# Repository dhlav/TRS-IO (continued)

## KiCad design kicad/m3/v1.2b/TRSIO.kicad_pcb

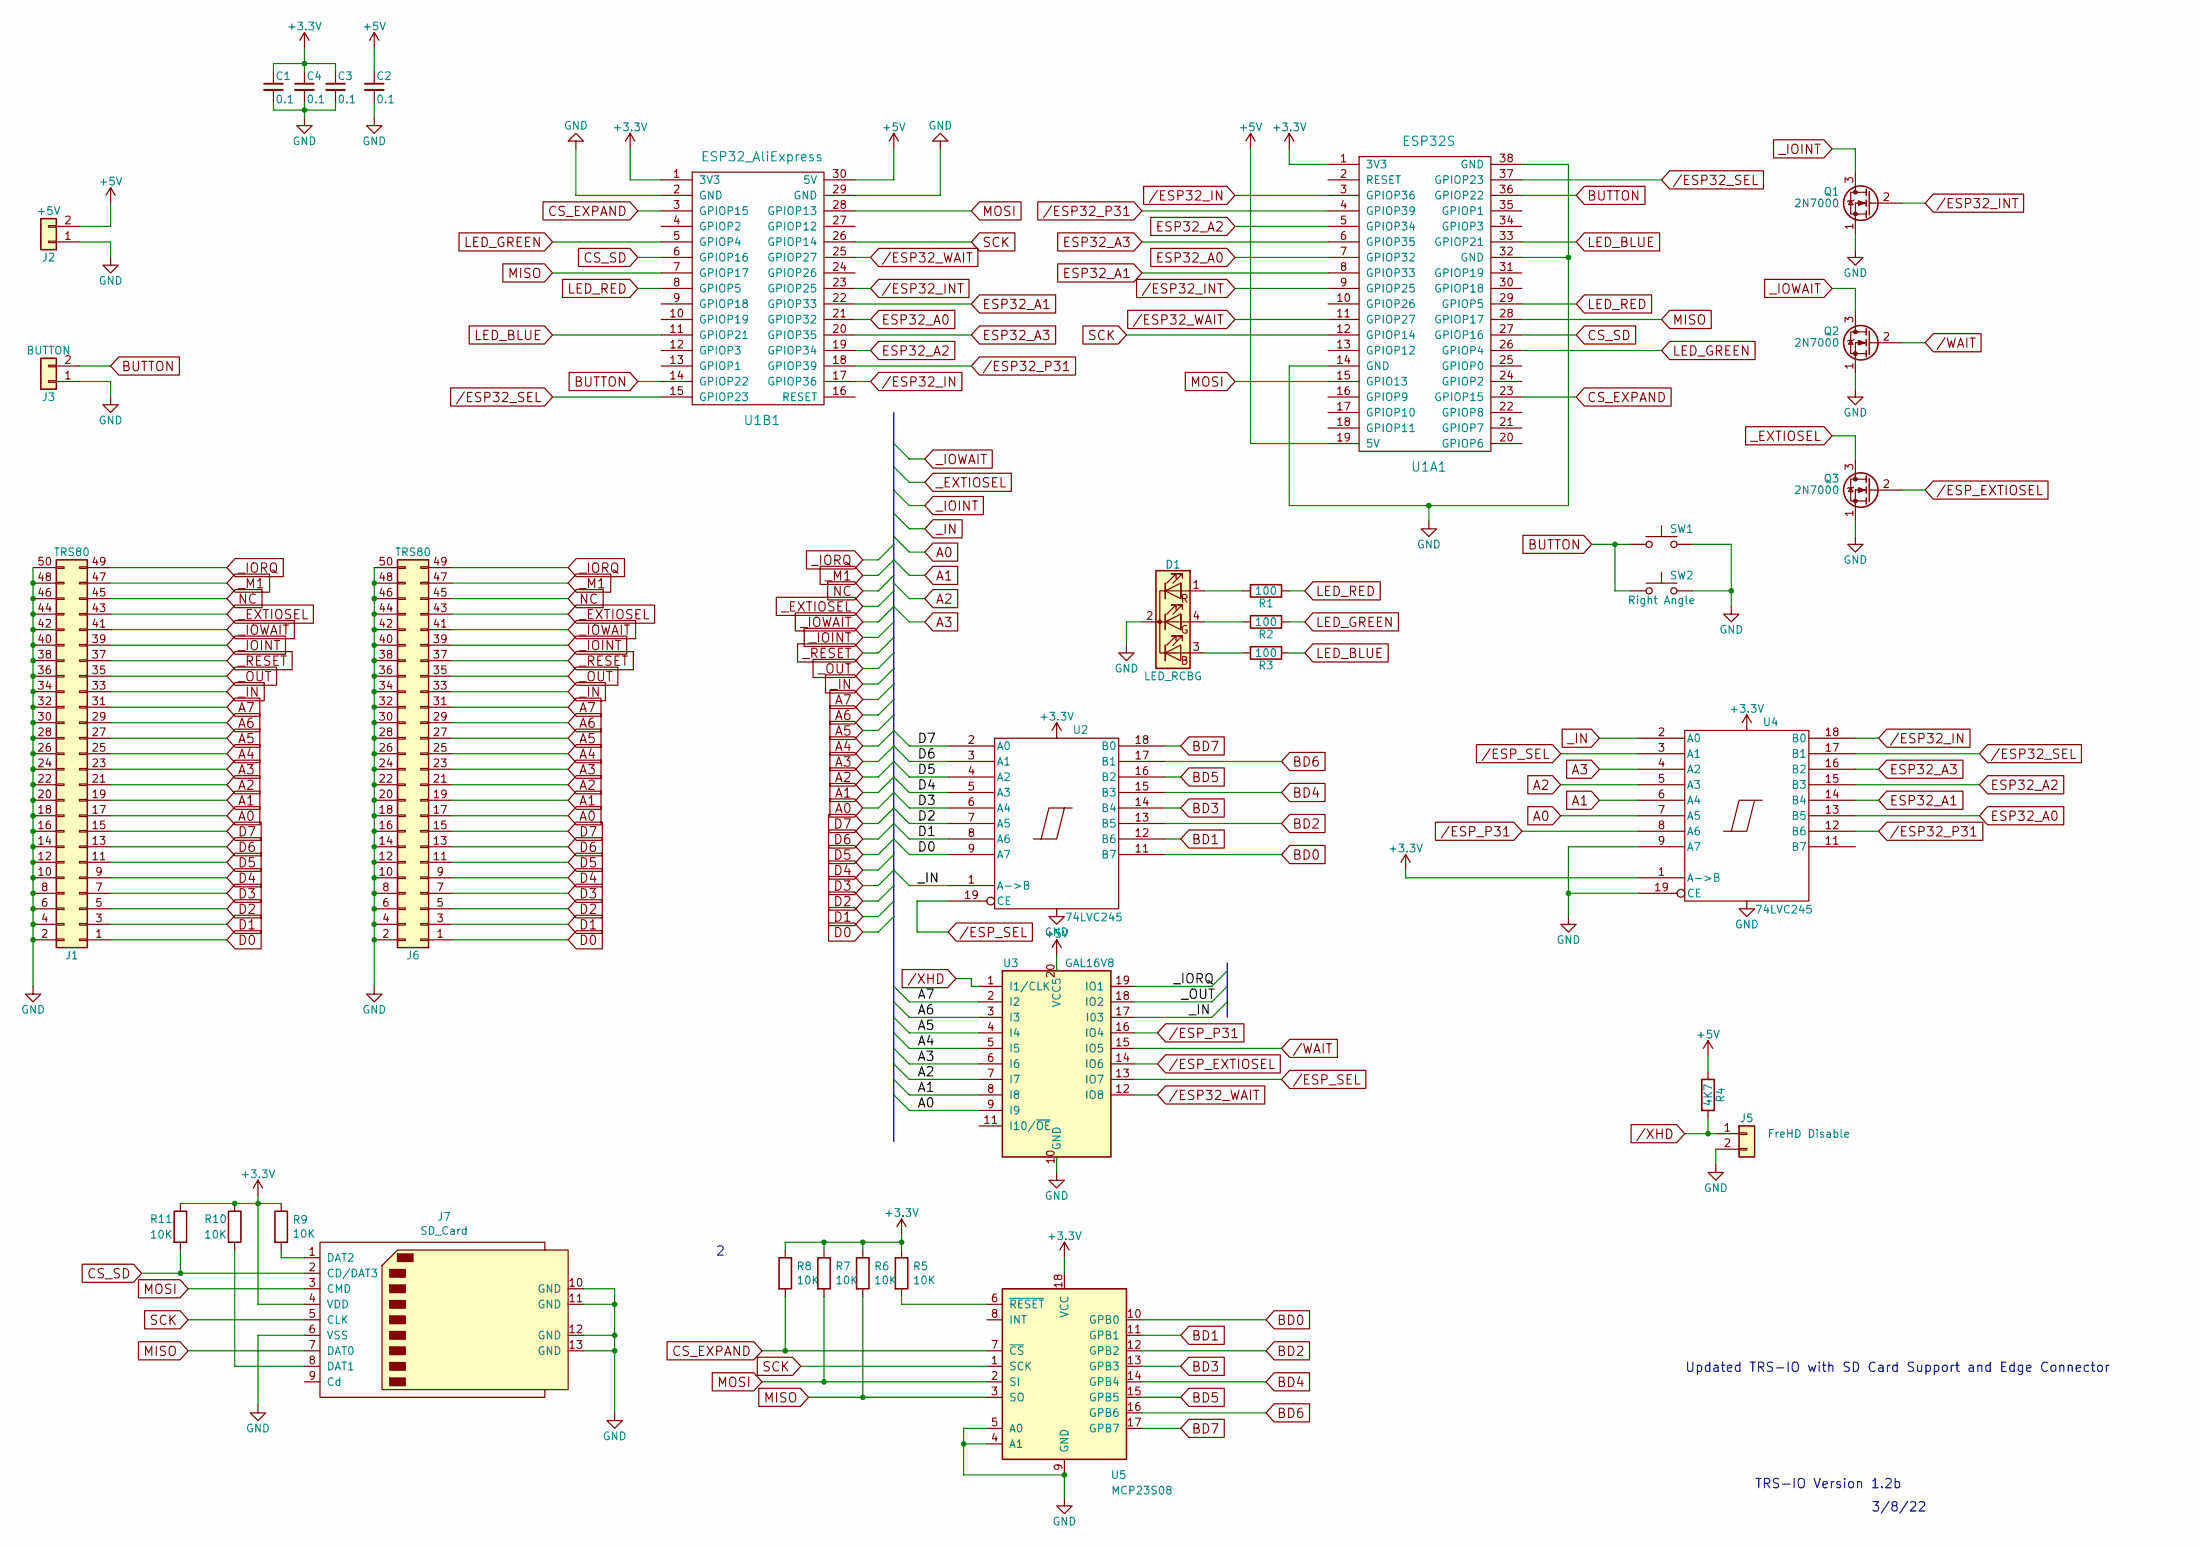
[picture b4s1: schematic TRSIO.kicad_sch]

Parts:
C1, C2, C3, C4: 0.1; C_Disc_D3.0mm_W2.0mm_P2.50mm
D1: LED_RCBG; LED_D5.0mm-4
J1: TRS80; Pin_Header_Straight_2x25_Pitch2.54mm
J2: +5V; Pin_Header_Straight_1x02_Pitch2.54mm
J3: BUTTON; Pin_Header_Straight_1x02_Pitch2.54mm
J5: FreHD Disable; Pin_Header_Straight_1x02_Pitch2.54mm
J6: TRS80; EDGE50
J7: SD_Card; TFP09-2-12B
Q1, Q2, Q3: 2N7000; TO-92_Molded_Narrow
R1, R2, R3: 100; R_Axial_DIN0207_L6.3mm_D2.5mm_P7.62mm_Horizontal
R4: 4K7; R_Axial_DIN0207_L6.3mm_D2.5mm_P7.62mm_Horizontal
R5, R6, R7, R8, R9, R10, R11: 10K; R_Axial_DIN0207_L6.3mm_D2.5mm_P7.62mm_Horizontal
SW1: SW_Push; SW_PUSH_6mm_h9.5mm
SW2: Right Angle; SW_Tactile_SPST_Angled_PTS645Vx31-2LFS
U1A1: ESP32S; DIP-38_W22.9mm
U1B1: ESP32_AliExpress; DIP-30_W25.4mm
U2, U4: 74LVC245; DIP-20_W7.62mm
U3: GAL16V8; DIP-20_W7.62mm
U5: MCP23S08; DIP-18_W7.62mm

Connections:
+3V3: C1.1, C3.1, C4.1, J7.4 (VDD), R5.1, R6.1, R7.1, R8.1, R9.1, R10.1, R11.1, U1A1.1 (3V3), U1B1.1 (3V3), U2.20 (VCC), U4.1 (A->B), U4.20 (VCC), U5.18 (VCC)
+5V: C2.1, J2.2, R4.1, U1A1.19 (5V), U1B1.30 (5V), U3.20 (VCC5)
A0: J1.17, J6.17, U3.9 (I9), U4.7 (A5)
A1: J1.19, J6.19, U3.8 (I8), U4.6 (A4)
A2: J1.21, J6.21, U3.7 (I7), U4.5 (A3)
A3: J1.23, J6.23, U3.6 (I6), U4.4 (A2)
A4: J1.25, J6.25, U3.5 (I5)
A5: J1.27, J6.27, U3.4 (I4)
A6: J1.29, J6.29, U3.3 (I3)
A7: J1.31, J6.31, U3.2 (I2)
BD0: U2.11 (B7), U5.10 (GPB0)
BD1: U2.12 (B6), U5.11 (GPB1)
BD2: U2.13 (B5), U5.12 (GPB2)
BD3: U2.14 (B4), U5.13 (GPB3)
BD4: U2.15 (B3), U5.14 (GPB4)
BD5: U2.16 (B2), U5.15 (GPB5)
BD6: U2.17 (B1), U5.16 (GPB6)
BD7: U2.18 (B0), U5.17 (GPB7)
BUTTON: J3.2, SW1.1, SW2.1, U1A1.36 (GPIOP22), U1B1.14 (GPIOP22)
CS_EXPAND: R8.2, U1A1.23 (GPIOP15), U1B1.3 (GPIOP15), U5.7 (~CS)
CS_SD: J7.2 (CD/DAT3), R11.2, U1A1.27 (GPIOP16), U1B1.6 (GPIOP16)
D0: J1.1, J6.1, U2.9 (A7)
D1: J1.3, J6.3, U2.8 (A6)
D2: J1.5, J6.5, U2.7 (A5)
D3: J1.7, J6.7, U2.6 (A4)
D4: J1.9, J6.9, U2.5 (A3)
D5: J1.11, J6.11, U2.4 (A2)
D6: J1.13, J6.13, U2.3 (A1)
D7: J1.15, J6.15, U2.2 (A0)
ESP32_A0: U1A1.7 (GPIOP32), U1B1.21 (GPIOP32), U4.13 (B5)
ESP32_A1: U1A1.8 (GPIOP33), U1B1.22 (GPIOP33), U4.14 (B4)
ESP32_A2: U1A1.5 (GPIOP34), U1B1.19 (GPIOP34), U4.15 (B3)
ESP32_A3: U1A1.6 (GPIOP35), U1B1.20 (GPIOP35), U4.16 (B2)
GND: C1.2, C2.2, C3.2, C4.2, D1.2 (K), J1.2, J1.4, J1.6, J1.8, J1.10, J1.12, J1.14, J1.16, J1.18, J1.20, J1.22, J1.24, J1.26, J1.28, J1.30, J1.32, J1.34, J1.36, J1.38, J1.40, J1.42, J1.44, J1.46, J1.48, J1.50, J2.1, J3.1, J5.2, J6.2, J6.4, J6.6, J6.8, J6.10, J6.12, J6.14, J6.16, J6.18, J6.20, J6.22, J6.24, J6.26, J6.28, J6.30, J6.32, J6.34, J6.36, J6.38, J6.40, J6.42, J6.44, J6.46, J6.48, J6.50, J7.6 (VSS), J7.10 (GND), J7.11 (GND), J7.12 (GND), J7.13 (GND), Q1.1 (S), Q2.1 (S), Q3.1 (S), SW1.2, SW2.2, U1A1.14 (GND), U1A1.32 (GND), U1A1.38 (GND), U1B1.2 (GND), U1B1.29 (GND), U2.10 (GND), U3.10 (GND), U4.9 (A7), U4.10 (GND), U4.19 (CE), U5.4 (A1), U5.5 (A0), U5.9 (GND)
LED_BLUE: R3.1, U1A1.33 (GPIOP21), U1B1.11 (GPIOP21)
LED_GREEN: R2.1, U1A1.26 (GPIOP4), U1B1.5 (GPIOP4)
LED_RED: R1.1, U1A1.29 (GPIOP5), U1B1.8 (GPIOP5)
MISO: J7.7 (DAT0), R6.2, U1A1.28 (GPIOP17), U1B1.7 (GPIOP17), U5.3 (SO)
MOSI: J7.3 (CMD), R7.2, U1A1.15 (GPIO13), U1B1.28 (GPIOP13), U5.2 (SI)
NC: J1.45, J6.45
unnamed: D1.1 (RA), R1.2
unnamed: D1.3 (BA), R3.2
unnamed: D1.4 (GA), R2.2
unnamed: J7.1 (DAT2), R9.2
unnamed: J7.8 (DAT1), R10.2
unnamed: R5.2, U5.6 (~RESET)
SCK: J7.5 (CLK), U1A1.12 (GPIOP14), U1B1.26 (GPIOP14), U5.1 (SCK)
_EXTIOSEL: J1.43, J6.43, Q3.3 (D)
_IN: J1.33, J6.33, U2.1 (A->B), U3.17 (I03), U4.2 (A0)
_IOINT: J1.39, J6.39, Q1.3 (D)
_IORQ: J1.49, J6.49, U3.19 (IO1)
_IOWAIT: J1.41, J6.41, Q2.3 (D)
_M1: J1.47, J6.47
_OUT: J1.35, J6.35, U3.18 (IO2)
_RESET: J1.37, J6.37
/ESP32_IN: U1A1.3 (GPIOP36), U1B1.17 (GPIOP36), U4.18 (B0)
/ESP32_INT: Q1.2 (G), U1A1.9 (GPIOP25), U1B1.23 (GPIOP25)
/ESP32_P31: U1A1.4 (GPIOP39), U1B1.18 (GPIOP39), U4.12 (B6)
/ESP32_SEL: U1A1.37 (GPIOP23), U1B1.15 (GPIOP23), U4.17 (B1)
/ESP32_WAIT: U1A1.11 (GPIOP27), U1B1.25 (GPIOP27), U3.12 (IO8)
/ESP_EXTIOSEL: Q3.2 (G), U3.14 (IO6)
/ESP_P31: U3.16 (IO4), U4.8 (A6)
/ESP_SEL: U2.19 (CE), U3.13 (IO7), U4.3 (A1)
/WAIT: Q2.2 (G), U3.15 (IO5)
/XHD: J5.1, R4.2, U3.1 (I1/CLK)

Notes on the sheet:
TRS-IO Version 1.2b
Updated TRS-IO with SD Card Support and Edge Connector
3/8/22

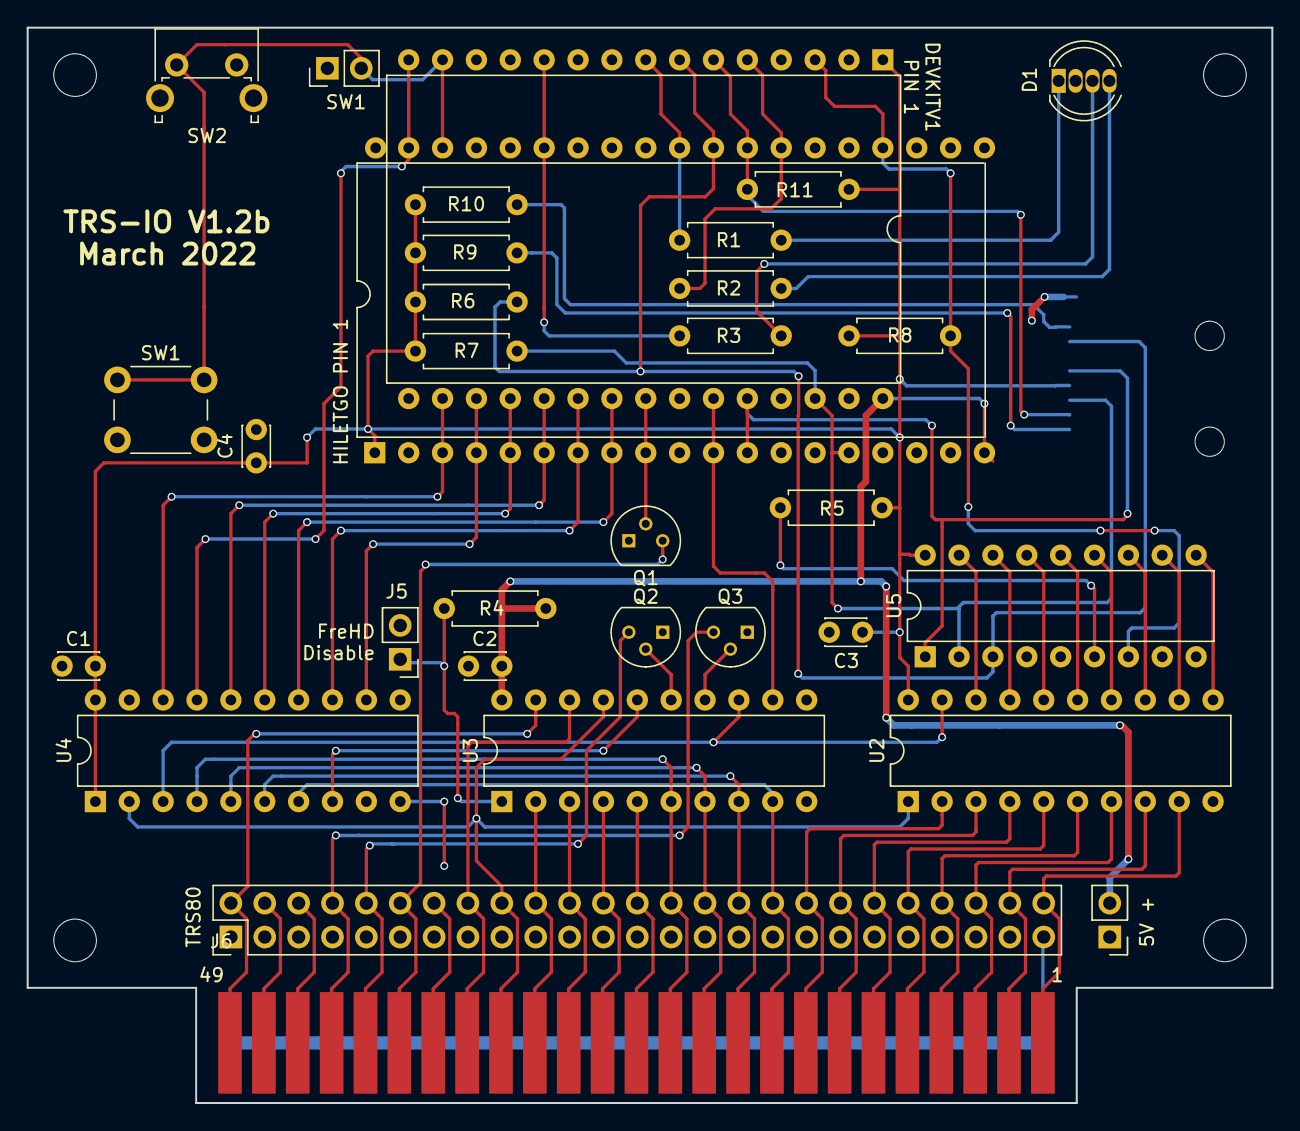
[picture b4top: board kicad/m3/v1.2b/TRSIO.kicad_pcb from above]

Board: 2 copper layers, 93.3 x 80.6 mm, 33 parts (1 on the bottom side), 65 nets.

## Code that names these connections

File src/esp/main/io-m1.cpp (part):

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#define GPIO_DATA_BUS_MASK 0b11111111000000000000

#ifdef CONFIG_TRS_IO_MODEL_1
#define ESP_S0 34
#define ESP_S1 35
#define IOBUSINT_N 33
#define ESP_SEL_N 27
#define ESP_WAIT_RELEASE_N 2
#else
// GPIO(23): ESP_SEL_N (TRS-IO or Frehd)
#define ESP_SEL_TRS_IO 39
#define IOBUSINT_N 25
#define ESP_SEL_N 23
#define ESP_WAIT_RELEASE_N 27
#endif

#define ESP_READ_N 36

#define ADJUST(x) ((x) < 32 ? (x) : (x) - 32)

#define MASK_ESP_SEL_N (1 << ADJUST(ESP_SEL_N))
#define MASK64_ESP_SEL_N (1ULL << ESP_SEL_N)
#ifdef CONFIG_TRS_IO_MODEL_1
#define MASK_ESP_S0 (1 << ADJUST(ESP_S0))
#define MASK64_ESP_S0 (1ULL << ESP_S0)
#define MASK_ESP_S1 (1 << ADJUST(ESP_S1))
#define MASK64_ESP_S1 (1ULL << ESP_S1)
#else
#define MASK_ESP_SEL_TRS_IO (1 << ADJUST(ESP_SEL_TRS_IO))
#define MASK64_ESP_SEL_TRS_IO (1ULL << ESP_SEL_TRS_IO)
#endif
#define MASK_ESP_WAIT_RELEASE_N (1 << ADJUST(ESP_WAIT_RELEASE_N))
#define MASK64_ESP_WAIT_RELEASE_N (1ULL << ESP_WAIT_RELEASE_N)
#define MASK_IOBUSINT_N (1 << ADJUST(IOBUSINT_N))
#define MASK64_IOBUSINT_N (1ULL << IOBUSINT_N)
#define MASK_ESP_READ_N (1 << ADJUST(ESP_READ_N))
#define MASK64_ESP_READ_N (1ULL << ESP_READ_N)

#define GPIO_OUTPUT_DISABLE(mask) GPIO.enable_w1tc = (mask)

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  gpio_set_level((gpio_num_t) IOBUSINT_N, 0);
  
  // Set ESP_WAIT_RELEASE_N to 0
  gpio_set_level((gpio_num_t) ESP_WAIT_RELEASE_N, 0);

#ifdef CONFIG_TRS_IO_MODEL_1
  TimerHandle_t timer = xTimerCreate("Heartbeat", 25, pdTRUE, NULL, timer25ms);
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
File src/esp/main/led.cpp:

#include "led.h"
#include "driver/gpio.h"
#include "freertos/FreeRTOS.h"
#include "freertos/task.h"
#include "freertos/event_groups.h"

#define LED_RED CONFIG_TRS_IO_GPIO_LED_RED
#define LED_GREEN CONFIG_TRS_IO_GPIO_LED_GREEN
#define LED_BLUE CONFIG_TRS_IO_GPIO_LED_BLUE
#define LED_SEL_MASK ((1ULL << LED_RED) | (1ULL << LED_GREEN) | (1ULL << LED_BLUE))

#define BIT_R BIT0
#define BIT_G BIT1
#define BIT_B BIT2

#define BIT_BLINK BIT3
#define BIT_AUTO_OFF BIT4

#define BIT_TRIGGER BIT5

static TaskHandle_t task_handle;
static EventGroupHandle_t event_group;


#ifdef CONFIG_TRS_IO_TEST_LED
static void test_led()
{
  while(1) {
    // First blink twice in white
    set_led(true, true, true, false, false);
    vTaskDelay(500 / portTICK_PERIOD_MS);
    set_led(false, false, false, false, false);
    vTaskDelay(500 / portTICK_PERIOD_MS);
    set_led(true, true, true, false, false);
    vTaskDelay(500 / portTICK_PERIOD_MS);
    set_led(false, false, false, false, false);
    vTaskDelay(500 / portTICK_PERIOD_MS);

    // Red
    set_led(true, false, false, false, false);
    vTaskDelay(1000 / portTICK_PERIOD_MS);
    // Green
    set_led(false, true, false, false, false);
    vTaskDelay(1000 / portTICK_PERIOD_MS);
    // Blue
    set_led(false, false, true, false, false);
    vTaskDelay(1000 / portTICK_PERIOD_MS);
  }
}
#endif
    

static void led_task(void* p)
{
  TickType_t delay = portMAX_DELAY;
  uint32_t r = 0;
  uint32_t g = 0;
  uint32_t b = 0;
  bool on = false;
  bool auto_off = false;
  
  while(true) {
    EventBits_t bits = xEventGroupWaitBits(event_group,
                                           BIT_R | BIT_G | BIT_B |
                                           BIT_BLINK | BIT_AUTO_OFF |
                                           BIT_TRIGGER,
                                           pdTRUE, // Clear on exit
                                           pdFALSE, // Wait for all bits
                                           delay);
    if (bits != 0) {
      r = (bits & BIT_R) ? 1 : 0;
      g = (bits & BIT_G) ? 1 : 0;
      b = (bits & BIT_B) ? 1 : 0;
      delay = (bits & BIT_BLINK) ? 500 / portTICK_PERIOD_MS : portMAX_DELAY;
      auto_off = bits & BIT_AUTO_OFF;
      if (auto_off) {
        delay = 3000 / portTICK_PERIOD_MS;
      }
      on = true;
    }

    if (on) {
      gpio_set_level((gpio_num_t) LED_RED, r);
      gpio_set_level((gpio_num_t) LED_GREEN, g);
      gpio_set_level((gpio_num_t) LED_BLUE, b);
    } else {
      gpio_set_level((gpio_num_t) LED_RED, 0);
      gpio_set_level((gpio_num_t) LED_GREEN, 0);
      gpio_set_level((gpio_num_t) LED_BLUE, 0);
      if (auto_off) {
        delay = portMAX_DELAY;
      }
    }
    on = !on;
  }
}

void init_led()
{
  gpio_config_t gpioConfig;

  // Configure LED
  gpioConfig.pin_bit_mask = LED_SEL_MASK;
  gpioConfig.mode = GPIO_MODE_OUTPUT;
  gpioConfig.intr_type = GPIO_INTR_DISABLE;
  gpio_config(&gpioConfig);

  event_group = xEventGroupCreate();
  xEventGroupClearBits(event_group, 0xff);
  xTaskCreatePinnedToCore(led_task, "led", 2048, NULL, 1, &task_handle, 0);
  
  // Turn LED off
  set_led(false, false, false, false, false);
#ifdef CONFIG_TRS_IO_TEST_LED
  test_led();
#endif
}
    

void set_led(bool r, bool g, bool b, bool blink, bool auto_off)
{
  EventBits_t mask = BIT_TRIGGER;

  if (r) {
    mask |= BIT_R;
  }
  if (g) {
    mask |= BIT_G;
  }
  if (b) {
    mask |= BIT_B;
  }
  if (blink) {
    mask |= BIT_BLINK;
  }
  if (auto_off) {
    mask |= BIT_AUTO_OFF;
  }
  xEventGroupSetBits(event_group, mask);
}

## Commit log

2022-11-12 Changes from fork and my local stuff
2022-11-16 Revert "Changes from fork and my local stuff"
    This reverts commit 389a2e327e33277d89ec96be275a46e34e0f8076.
2022-11-16 Add build instructions file.
2022-11-16 Changes md5 dup issue
2022-11-16 Removed submodule libsmb2
2022-11-16 Finally added static libsmb2 repo to mine. Need to make a change to check for ESP_PLATFORM for md5 - was creating duplicate symbols
2023-02-14 Branch reverted to just before combining spi and io since model 1 sd card without fpga had been removed in tip. Will have to cherry pick commits going forward from remote.
